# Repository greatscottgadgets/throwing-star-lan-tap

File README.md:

# Throwing Star LAN TAP

A passive tap for monitoring 10/100 Ethernet.

## parts required:
 * qty 4 RJ45 connectors: Amphenol RJHSE-5080 (unshielded) or RJHSE-5380 (shielded)
 * qty 2 220pF through-hole capacitors with .1" lead spacing (e.g. KEMET C315C221K1G5TA)

These design files are licensed under the terms in the file, LICENSE.

For more information: https://greatscottgadgets.com/throwingstar/

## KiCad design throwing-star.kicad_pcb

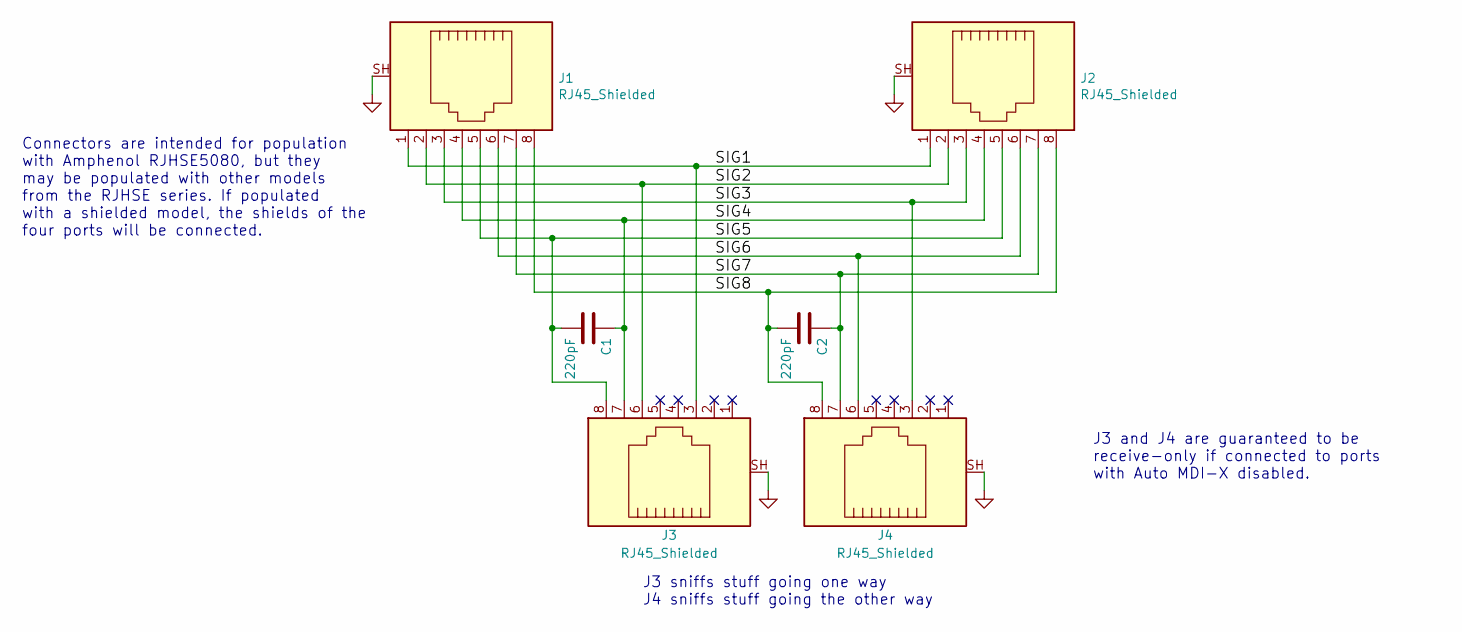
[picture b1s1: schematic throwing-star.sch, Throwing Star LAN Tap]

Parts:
C1, C2: 220pF; C_Disc_D5.0mm_W2.5mm_P2.50mm; Part Number C315C221K1G5TA
J1, J2, J3, J4: RJ45_Shielded; RJ45_Amphenol_RJHSE538X_TSLT; Part Number RJHSE5080

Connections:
/SIG1: J1.1, J2.1, J3.3
/SIG2: J1.2, J2.2, J3.6
/SIG3: J1.3, J2.3, J4.3
/SIG4: C1.1, J1.4, J2.4, J3.7
/SIG5: C1.2, J1.5, J2.5, J3.8
/SIG6: J1.6, J2.6, J4.6
/SIG7: C2.1, J1.7, J2.7, J4.7
/SIG8: C2.2, J1.8, J2.8, J4.8
GND: J1.SH, J2.SH, J3.SH, J4.SH

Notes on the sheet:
J3 sniffs stuff going one way J4 sniffs stuff going the other way
Connectors are intended for population with Amphenol RJHSE5080, but they may be populated with other models from the RJHSE series. If populated with a shielded model, the shields of the four ports will be connected.
J3 and J4 are guaranteed to be receive-only if connected to ports with Auto MDI-X disabled.

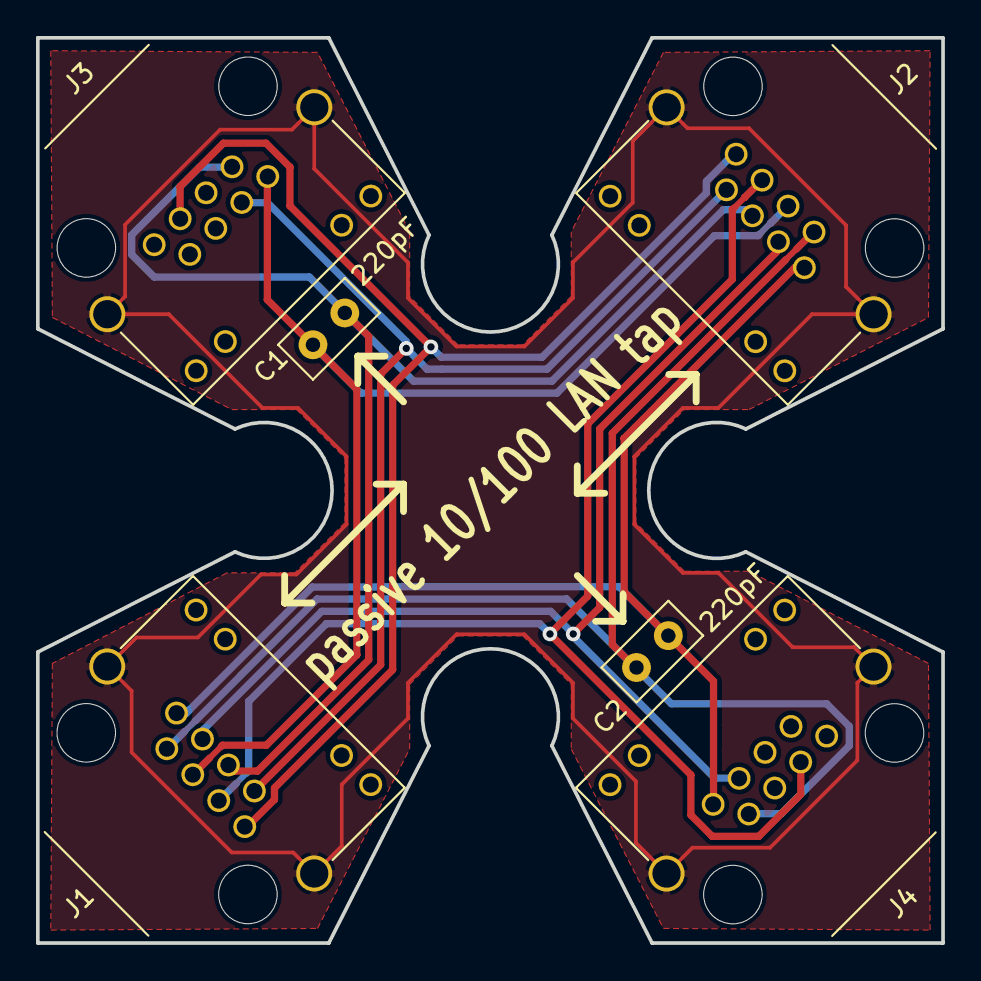
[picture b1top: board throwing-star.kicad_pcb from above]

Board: 2 copper layers, 50.3 x 50.3 mm, 6 parts (0 on the bottom side), 9 nets.

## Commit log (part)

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2018-04-11 Initial commit of TSLT design files from 2011 tar archive
2020-07-27 update license to CERN-OHL-P v2
2020-07-28 add Throwing Star LAN Tap Pro layout
2021-10-28 s/kicad-pcb.org/kicad.org/

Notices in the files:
throwing-star.kicad_pcb:
Copyright (c) 2010-2020 Great Scott Gadgets
Licensed under the CERN-OHL-P v2
